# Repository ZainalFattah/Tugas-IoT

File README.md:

# Kelompok 7 — UdaraKita

Proyek IoT untuk memantau kondisi udara menggunakan NodeMCU ESP8266, sensor DHT11, dan sensor gas MQ-135. Data dikirim ke Blynk melalui Wi-Fi.

## Anggota

- Zainal Fattah
- Naufal Adani
- Aisyha N A

## Versi perakitan

Versi final menggunakan **breadboard dan kabel jumper**, tanpa PCB khusus. Panduan kabel dan gambar rangkaian tersedia di:

- [Panduan perakitan breadboard](PANDUAN_PERAKITAN_BREADBOARD.md)
- [Skema perakitan berwarna](Skema_Perakitan_Breadboard.svg)
- [Daftar komponen dan rencana proyek](Rencana_Proyek.md)

## Menjalankan proyek

1. Buka [CARA_RUN_BLYNK.md](CARA_RUN_BLYNK.md) untuk menyiapkan template, datastream, dan dashboard Blynk.
2. Buka `Firmware/UdaraKitaBlynk/Config.h` di komputer sendiri.
3. Isi Wi-Fi dan Auth Token Blynk secara lokal, lalu upload firmware ke NodeMCU.
4. Jangan commit Auth Token atau kata sandi Wi-Fi ke repositori.

Firmware Blynk menggunakan pin berikut: DHT11 pada D2/GPIO4, LED hijau pada D5/GPIO14, LED merah pada D6/GPIO12, dan MQ-135 pada A0.

## Simulator web

Buka [simulator UdaraKita](simulator/index.html) untuk mencoba rangkaian dan alur indikator tanpa membeli perangkat terlebih dahulu. [Panduan menjalankan simulator](simulator/README.md) menjelaskan tiap langkah. Simulator menggunakan komponen dan jalur rangkaian asli, tetapi merupakan model perilaku lokal; pratinjau datastream tidak mengirim data ke Blynk.Cloud.

Versi web siap pakai: [UdaraKita Simulator](https://udarakita-kelompok7-simulator.jovialrose1.chatgpt.site/) (akses pemilik melalui masuk dengan ChatGPT).

## Lisensi

Lihat [LICENSE](LICENSE) dan [THIRD_PARTY.md](THIRD_PARTY.md).

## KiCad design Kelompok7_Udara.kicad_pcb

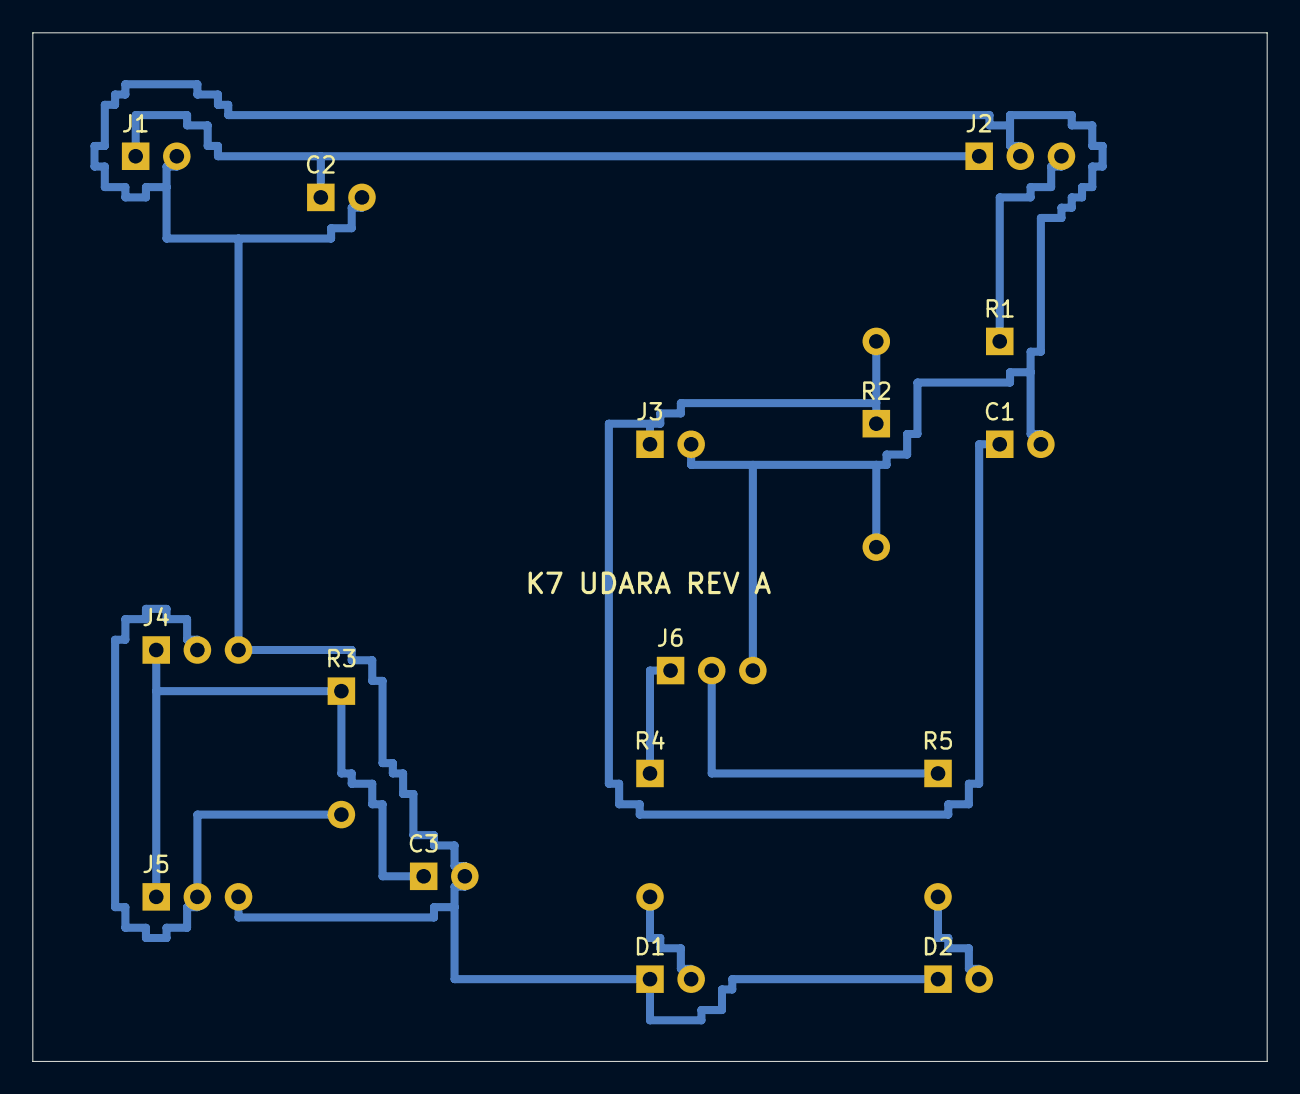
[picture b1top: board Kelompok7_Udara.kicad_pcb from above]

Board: 2 copper layers, 76.2 x 63.5 mm, 16 parts (0 on the bottom side), 10 nets.

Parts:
C1: 100nF; C1
C2: 100uF 10V; C2
C3: 100nF; C3
D1: GREEN K/A; D1
D2: RED K/A; D2
J1: 5V IN; J1
J2: MQ135; J2
J3: MCU A0/G; J3
J4: MCU 3V3/D2/G; J4
J5: DHT11; J5
J6: MCU D5/D6/G; J6
R1: 47k 1%; R1
R2: 10k 1%; R2
R3: 10k; R3
R4: 1k; R4
R5: 1k; R5

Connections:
3V3: C3.1, J4.1, J5.1, R3.1
5V: C2.1, J1.1, J2.1
ADC: C1.1, J3.1, R1.2, R2.1
D5: J6.1, R4.1
D6: J6.2, R5.1
DHT: J4.2, J5.2, R3.2
GND: C1.2, C2.2, C3.2, D1.1, D2.1, J1.2, J2.2, J3.2, J4.3, J5.3, J6.3, R2.2
LED_G: D1.2, R4.2
LED_R: D2.2, R5.2
MQ_AO: J2.3, R1.1
